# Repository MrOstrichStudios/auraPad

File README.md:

# auraPad
its a mini keypad filled with AURA for the **Hackpad mission on "Stardance Hackclub 2026"**
## what it has?  

it has a **4 key layout with a custom shell, working on the Seeed Studio RP2040** **, a rotary encoder with a switch, leds (**flashin**) and an oled with a bongo cat!!!** _meow_  
all keys can be modified with **VIA** (Google AI told me about it and it seems cool!!)
## hardest part for me? x_x
the hardest part for me would be the time i had to design the case for it. it took me more than **10** hours doing it!
## so is it cool?
**OFC**
## BOM:
- 4x Cherry MX Switches
- 4x DSA Keycaps
- 5x M3x16mm Screws
- 5x M3x5mx4mm Heatset inserts
- 1x 0.91 inch OLED Display
- 1x Seeed XIAO RP2040
- 1x EC11E Rotary Encoders
- 5x 1N4148 Diodes
- 2x SK6812 MINI-E LEDs
- 1x Case (3 Printed Parts)
- 1x PCB

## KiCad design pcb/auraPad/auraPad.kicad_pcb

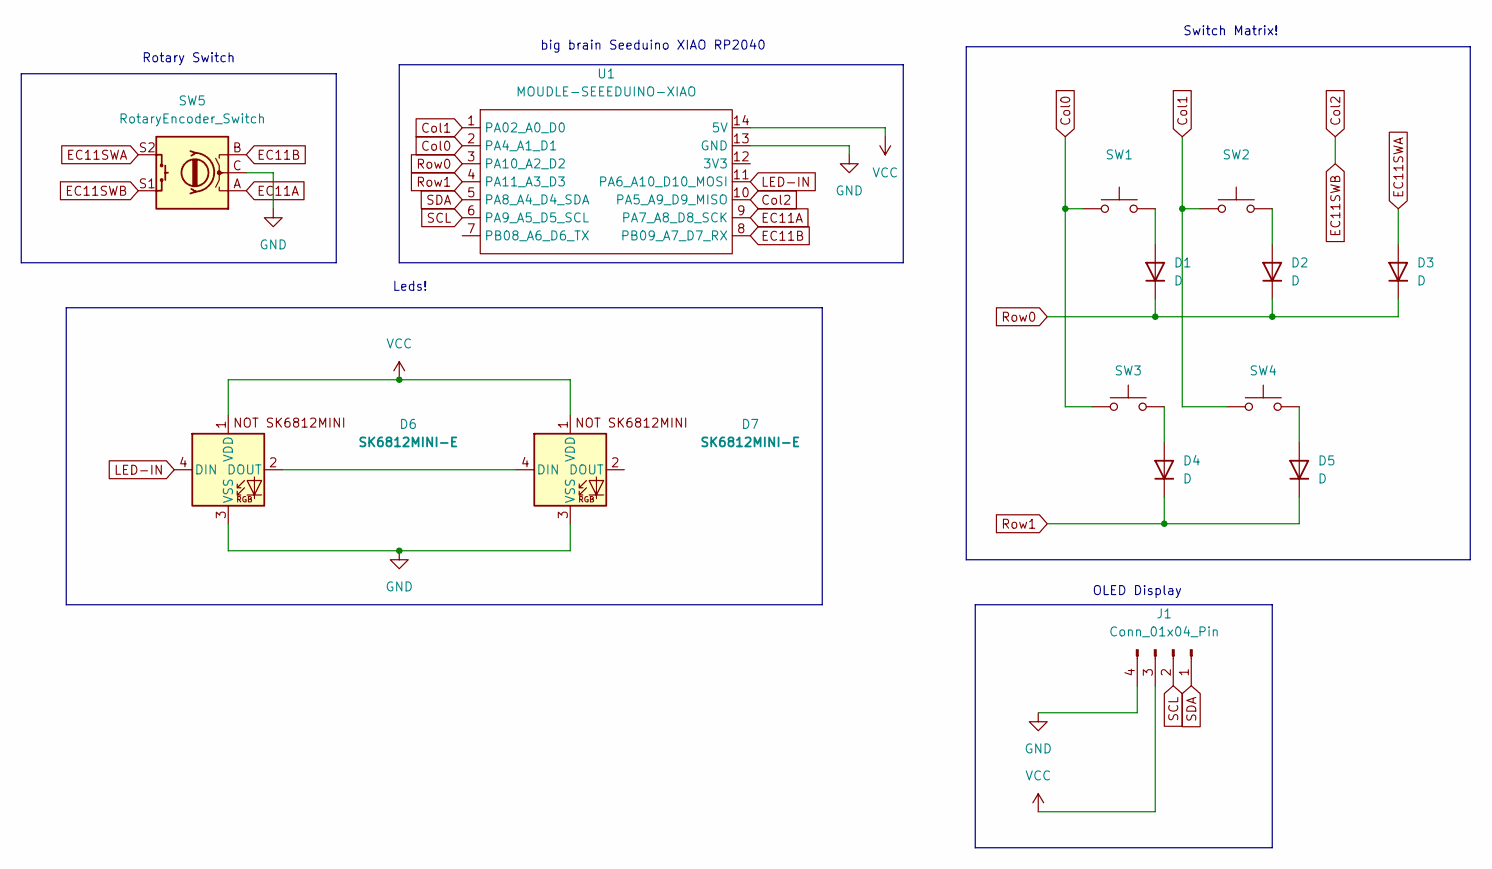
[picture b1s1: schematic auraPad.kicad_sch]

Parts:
D1, D2, D3, D4, D5: D; D_DO-35_SOD27_P7.62mm_Horizontal
D6, D7: SK6812MINI-E; SK6812MINI-E_fixed
J1: Conn_01x04_Pin; PinHeader_1x04_P2.54mm_Vertical
SW1, SW2, SW3, SW4: SW_Push; SW_Cherry_MX_1.00u_PCB
SW5: RotaryEncoder_Switch; RotaryEncoder_Alps_EC11E-Switch_Vertical_H20mm
U1: MOUDLE-SEEEDUINO-XIAO; XIAO-Generic-Hybrid-14P-2.54-21X17.8MM

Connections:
Col0: SW1.1, SW3.1, U1.2 (PA4_A1_D1)
Col1: SW2.1, SW4.1, U1.1 (PA02_A0_D0)
Col2: SW5.S1, U1.10 (PA5_A9_D9_MISO)
EC11A: SW5.A, U1.9 (PA7_A8_D8_SCK)
EC11B: SW5.B, U1.8 (PB09_A7_D7_RX)
EC11SWA: D3.2 (A), SW5.S2
GND: D6.3 (VSS), D7.3 (VSS), J1.4, SW5.C, U1.13 (GND)
LED-IN: D6.4 (DIN), U1.11 (PA6_A10_D10_MOSI)
unnamed: D1.2 (A), SW1.2
unnamed: D2.2 (A), SW2.2
unnamed: D4.2 (A), SW3.2
unnamed: D5.2 (A), SW4.2
unnamed: D6.2 (DOUT), D7.4 (DIN)
Row0: D1.1 (K), D2.1 (K), D3.1 (K), U1.3 (PA10_A2_D2)
Row1: D4.1 (K), D5.1 (K), U1.4 (PA11_A3_D3)
SCL: J1.2, U1.6 (PA9_A5_D5_SCL)
SDA: J1.1, U1.5 (PA8_A4_D4_SDA)
VCC: D6.1 (VDD), D7.1 (VDD), J1.3, U1.14 (5V)

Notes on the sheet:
OLED Display
Switch Matrix!
Leds!
big brain Seeduino XIAO RP2040
Rotary Switch

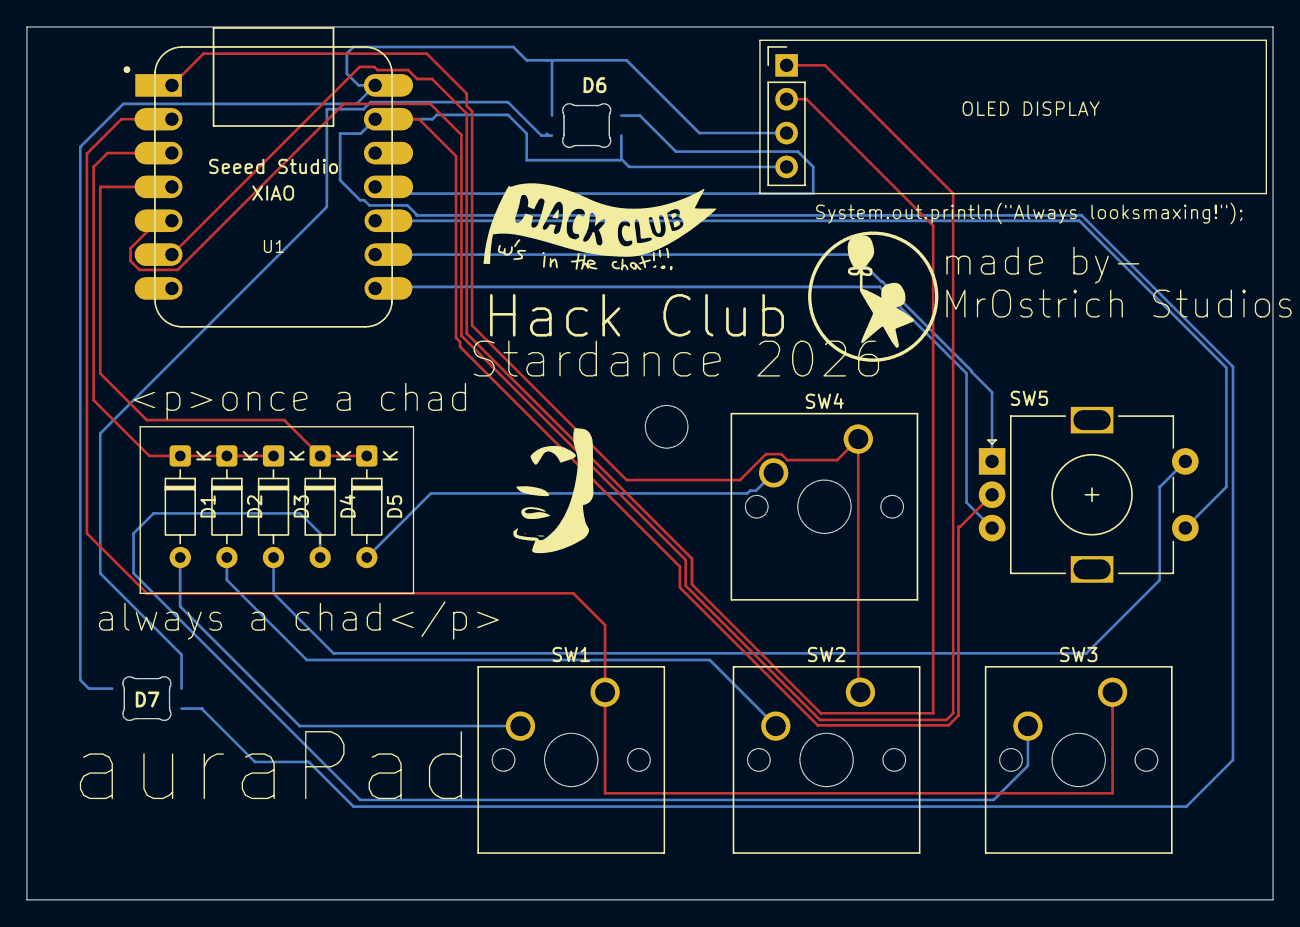
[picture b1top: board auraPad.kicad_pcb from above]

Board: 2 copper layers, 93.5 x 65.5 mm, 15 parts (0 on the bottom side), 18 nets.

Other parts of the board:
HACKCLUB: LOGO; fixed_long_live_Hackclub

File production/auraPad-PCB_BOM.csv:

"Id";"Designator";"Footprint";"Quantity";"Designation";"Supplier and ref";
1;"J1";"PinHeader_1x04_P2.54mm_Vertical";1;"Conn_01x04_Pin";;;
2;"SW2,SW4,SW1,SW3";"SW_Cherry_MX_1.00u_PCB";4;"SW_Push";;;
3;"D2,D1,D5,D3,D4";"D_DO-35_SOD27_P7.62mm_Horizontal";5;"D";;;
4;"D6,D7";"SK6812MINI-E_fixed";2;"SK6812MINI-E";;;
5;"U1";"XIAO-Generic-Hybrid-14P-2.54-21X17.8MM";1;"MOUDLE-SEEEDUINO-XIAO";;;
6;"SW5";"RotaryEncoder_Alps_EC11E-Switch_Vertical_H20mm";1;"RotaryEncoder_Switch";;;
